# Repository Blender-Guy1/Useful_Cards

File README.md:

# Useful_Cards
This is a repository that contains cards that are useful or fun. This includes business cards that can play Pong and cards that act as simple electronics equipment for troubleshooting on the road.

## The Different Cards

### Business Card that Plays [Pong](https://en.wikipedia.org/wiki/Pong)
This went through 3 iterations before I got one that work, and 5 before I felt comfortable showing this to other people. It is a business card PCB that runs on a button cell battery and can play a any games that will run on the microcontroller. All of which is controlled with an [STM32L010F4](https://www.digikey.com/en/products/detail/stmicroelectronics/STM32L010F4P6/10063389) (which isn't exactly necessary for this application as I am running it like any other STM32 microcontroller.). More information can be found in the readme.md in the folder named "Business Card".

### Why I wanted to make Business Cards

I exhibitted at [OpenSauce 2024](https://opensauce.com/) and had the pleasure to meet [Ben Eater](https://www.youtube.com/@BenEater). He handed me a business card that was a puzzle. When a CR2025 battery was inserted, the 8 LEDs on the PCB would blink "SHAKE ME" in ASCII. Once shaken, the card wrote Ben Eater in the air. This was by far the coolest electronics idea I had ever seen. This got me thinking for a while and eventually I decided to steal his idea and make a 3D holographic business card. But that would be pretty lazy and unoriginal, so I decided on something similar that was simple. This led me to creating a business card that could play pong.

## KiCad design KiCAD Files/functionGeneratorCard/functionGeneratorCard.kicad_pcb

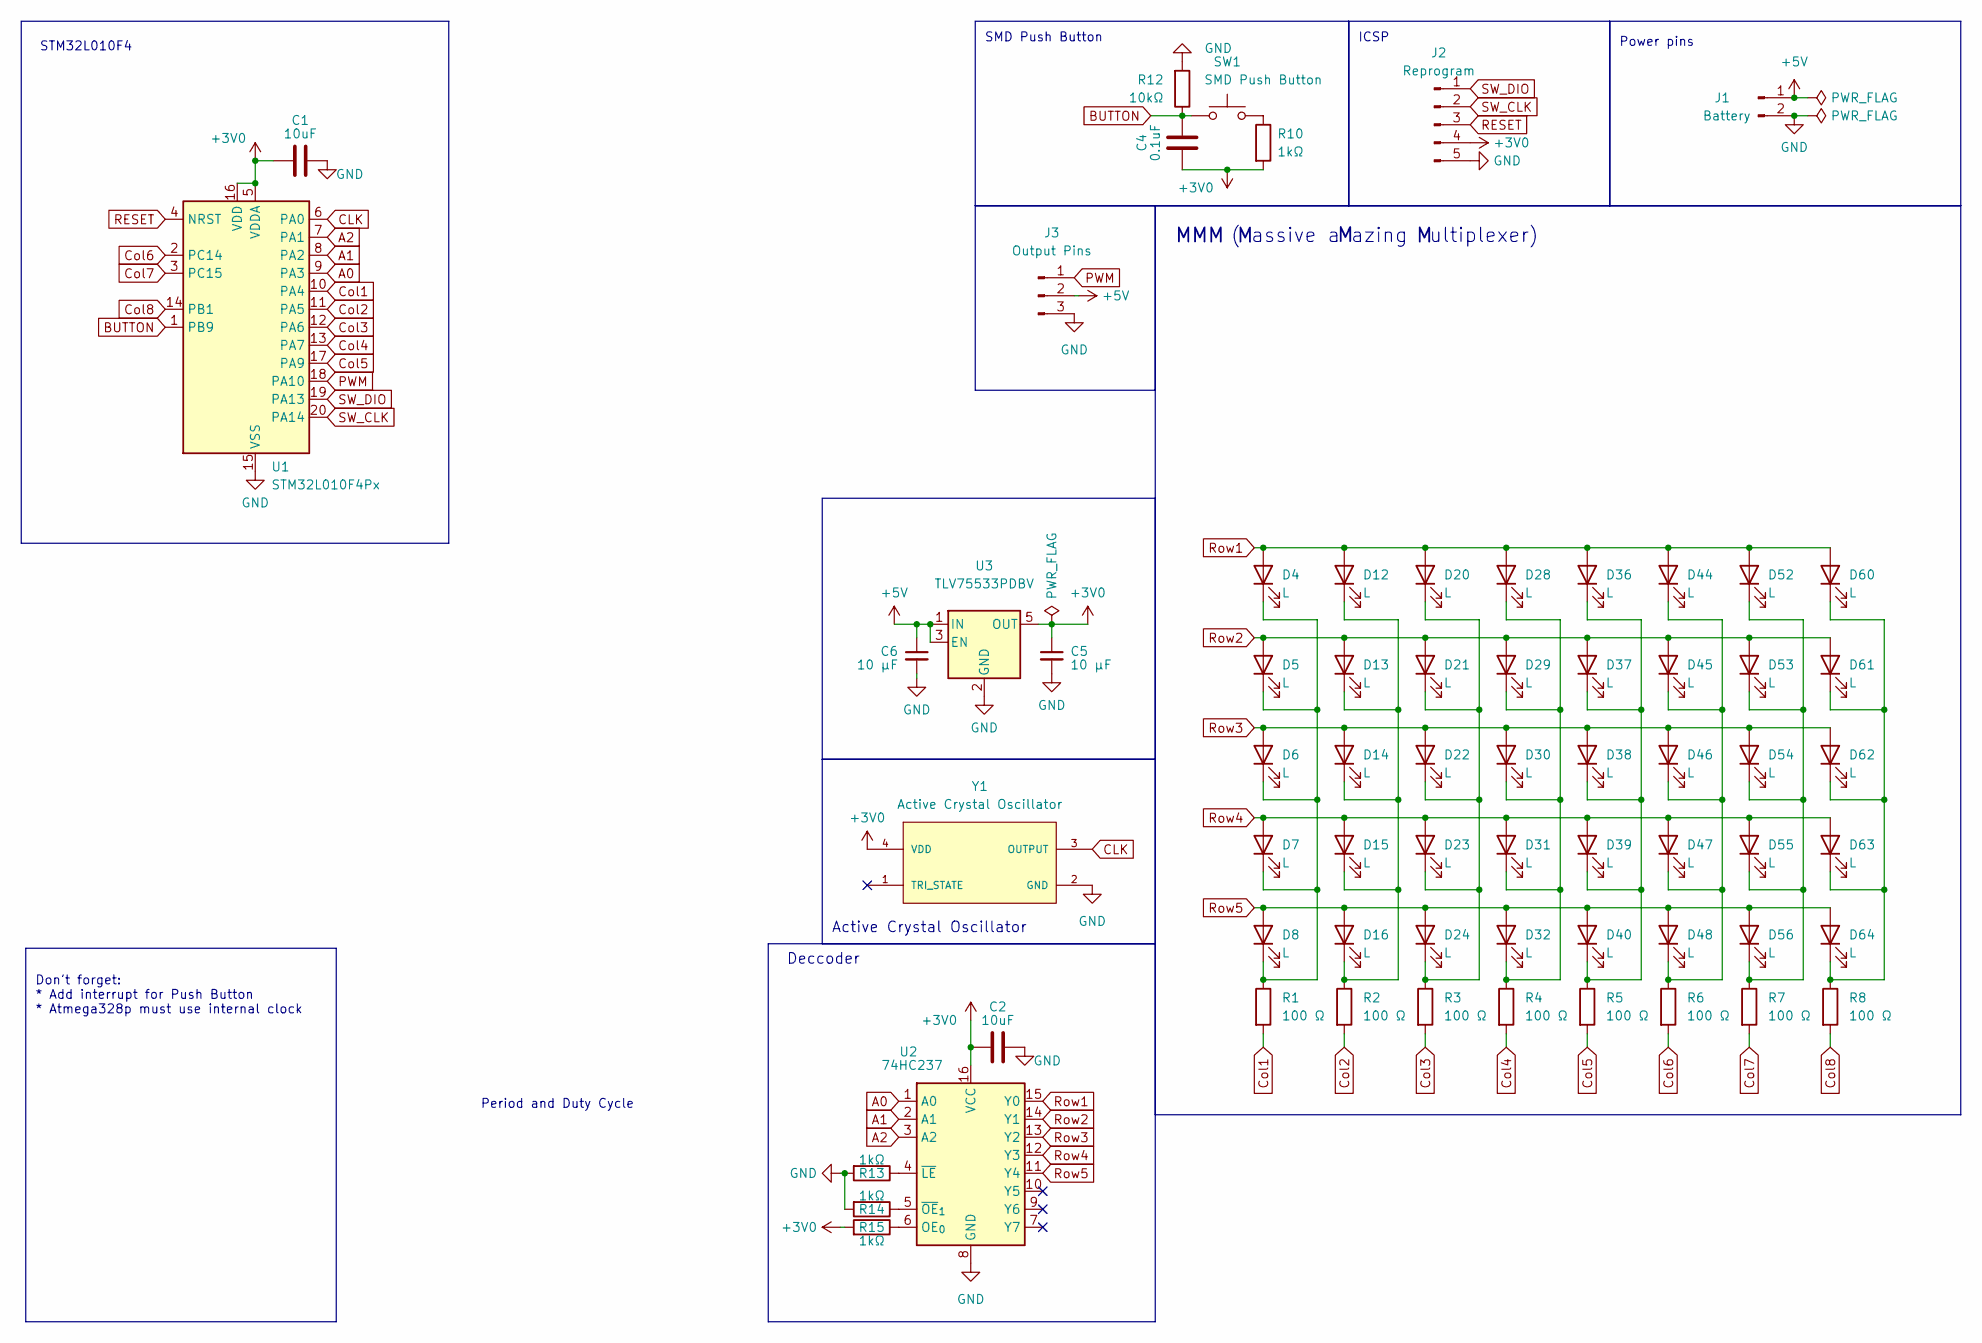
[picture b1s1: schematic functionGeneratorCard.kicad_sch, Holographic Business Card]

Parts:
C1, C2: 10uF; C_0603_1608Metric; LCSC C70225
C4: 0.1uF; C_0603_1608Metric; LCSC C1590
C5, C6: 10 µF; C_0603_1608Metric
D4, D5, D6, D7, D8, D12, D13, D14, D15, D16, D20, D21, D22, D23, D24, D28, D29, D30, D31, D32, D36, D37, D38, D39, D40, D44, D45, D46, D47, D48, D52, D53, D54, D55, D56, D60, D61, D62, D63, D64: L; LED_0805_2012Metric; LCSC C434431
J1: Battery; 2 Pin SMD (2.54)
J2: Reprogram; PinHeader_1x05_P2.54mm_Vertical
J3: Output Pins; 3 Pin SMD (2.54)
R1, R2, R3, R4, R5, R6, R7, R8: 100 Ω; R_0603_1608Metric; LCSC C3017758
R10, R13, R14, R15: 1kΩ; R_0603_1608Metric; LCSC C14676
R12: 10kΩ; R_0603_1608Metric; LCSC C15401
SW1: SMD Push Button; SW_SPST_TL3342; LCSC C2874421
U1: STM32L010F4Px; TSSOP-20_4.4x6.5mm_P0.65mm; LCSC C529415
U2: 74HC237; SOT-23-16 Thin
U3: TLV75533PDBV; SOT-23-5
Y1: Active Crystal Oscillator; active crystal oscillator; PARTREV 2017; LCSC C1857764

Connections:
+3V0: C1.1, C2.1, C4.1, C5.1, J2.4, R10.2, R15.2, U1.5 (VDDA), U1.16 (VDD), U2.16 (VCC), U3.5 (OUT), Y1.4 (VDD)
+5V: C6.1, J1.1, J3.2, U3.1 (IN), U3.3 (EN)
A0: U1.9 (PA3), U2.1 (A0)
A1: U1.8 (PA2), U2.2 (A1)
A2: U1.7 (PA1), U2.3 (A2)
BUTTON: C4.2, R12.1, SW1.1, U1.1 (PB9)
CLK: U1.6 (PA0), Y1.3 (OUTPUT)
Col1: R1.2, U1.10 (PA4)
Col2: R2.2, U1.11 (PA5)
Col3: R3.2, U1.12 (PA6)
Col4: R4.2, U1.13 (PA7)
Col5: R5.2, U1.17 (PA9)
Col6: R6.2, U1.2 (PC14)
Col7: R7.2, U1.3 (PC15)
Col8: R8.2, U1.14 (PB1)
GND: C1.2, C2.2, C5.2, C6.2, J1.2, J2.5, J3.3, R12.2, R13.2, R14.2, U1.15 (VSS), U2.8 (GND), U3.2 (GND), Y1.2 (GND)
unnamed: D4.1 (K), D5.1 (K), D6.1 (K), D7.1 (K), D8.1 (K), R1.1
unnamed: D12.1 (K), D13.1 (K), D14.1 (K), D15.1 (K), D16.1 (K), R2.1
unnamed: D20.1 (K), D21.1 (K), D22.1 (K), D23.1 (K), D24.1 (K), R3.1
unnamed: D28.1 (K), D29.1 (K), D30.1 (K), D31.1 (K), D32.1 (K), R4.1
unnamed: D36.1 (K), D37.1 (K), D38.1 (K), D39.1 (K), D40.1 (K), R5.1
unnamed: D44.1 (K), D45.1 (K), D46.1 (K), D47.1 (K), D48.1 (K), R6.1
unnamed: D52.1 (K), D53.1 (K), D54.1 (K), D55.1 (K), D56.1 (K), R7.1
unnamed: D60.1 (K), D61.1 (K), D62.1 (K), D63.1 (K), D64.1 (K), R8.1
unnamed: R10.1, SW1.2
unnamed: R15.1, U2.6 (OE_{0})
unnamed: R13.1, U2.4 (~LE)
unnamed: R14.1, U2.5 (~OE_{1})
PWM: J3.1, U1.18 (PA10)
RESET: J2.3, U1.4 (NRST)
Row1: D4.2 (A), D12.2 (A), D20.2 (A), D28.2 (A), D36.2 (A), D44.2 (A), D52.2 (A), D60.2 (A), U2.15 (Y0)
Row2: D5.2 (A), D13.2 (A), D21.2 (A), D29.2 (A), D37.2 (A), D45.2 (A), D53.2 (A), D61.2 (A), U2.14 (Y1)
Row3: D6.2 (A), D14.2 (A), D22.2 (A), D30.2 (A), D38.2 (A), D46.2 (A), D54.2 (A), D62.2 (A), U2.13 (Y2)
Row4: D7.2 (A), D15.2 (A), D23.2 (A), D31.2 (A), D39.2 (A), D47.2 (A), D55.2 (A), D63.2 (A), U2.12 (Y3)
Row5: D8.2 (A), D16.2 (A), D24.2 (A), D32.2 (A), D40.2 (A), D48.2 (A), D56.2 (A), D64.2 (A), U2.11 (Y4)
SW_CLK: J2.2, U1.20 (PA14)
SW_DIO: J2.1, U1.19 (PA13)

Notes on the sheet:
( assive a azing ultiplexer)
Don't forget: * Add interrupt for Push Button * Atmega328p must use internal clock
Deccoder
MMM
Period and Duty Cycle
Power pins
ICSP
Active Crystal Oscillator
STM32L010F4
SMD Push Button

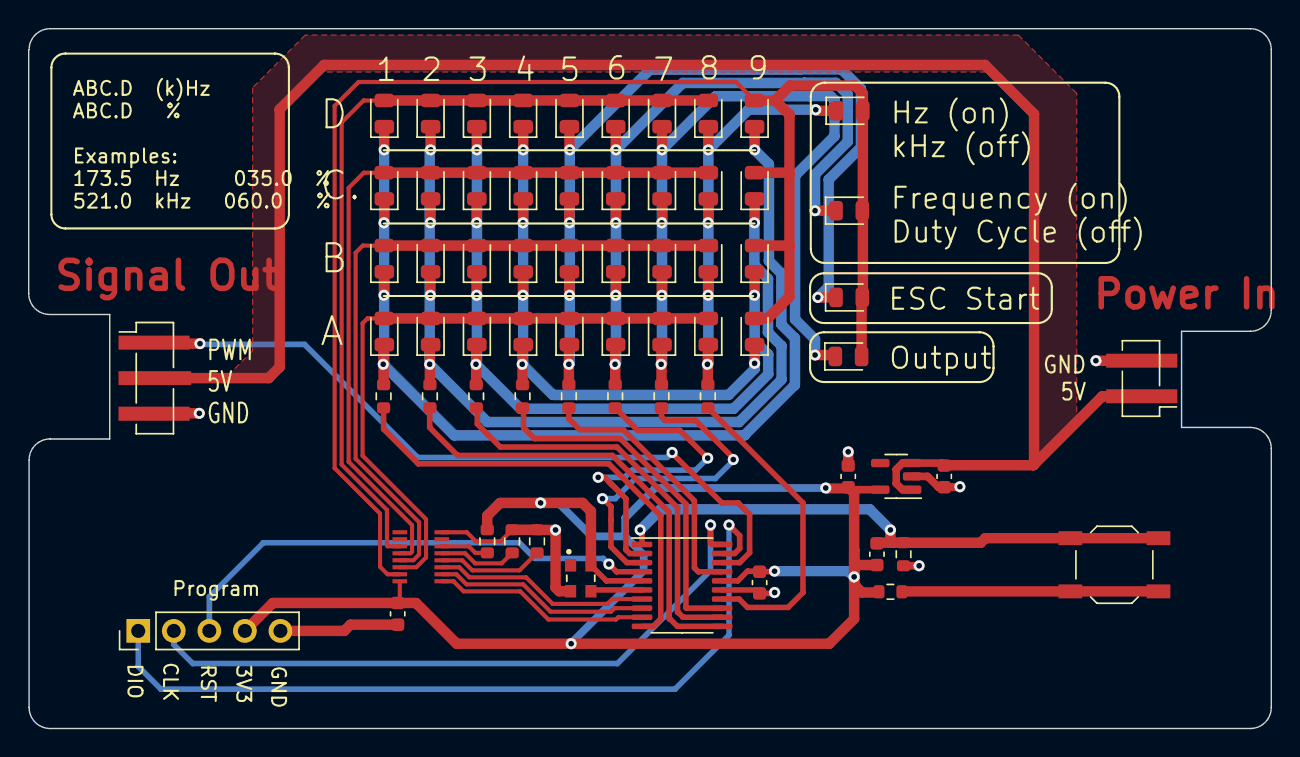
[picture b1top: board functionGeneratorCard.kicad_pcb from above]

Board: 2 copper layers, 88.8 x 50.0 mm, 66 parts (0 on the bottom side), 37 nets.

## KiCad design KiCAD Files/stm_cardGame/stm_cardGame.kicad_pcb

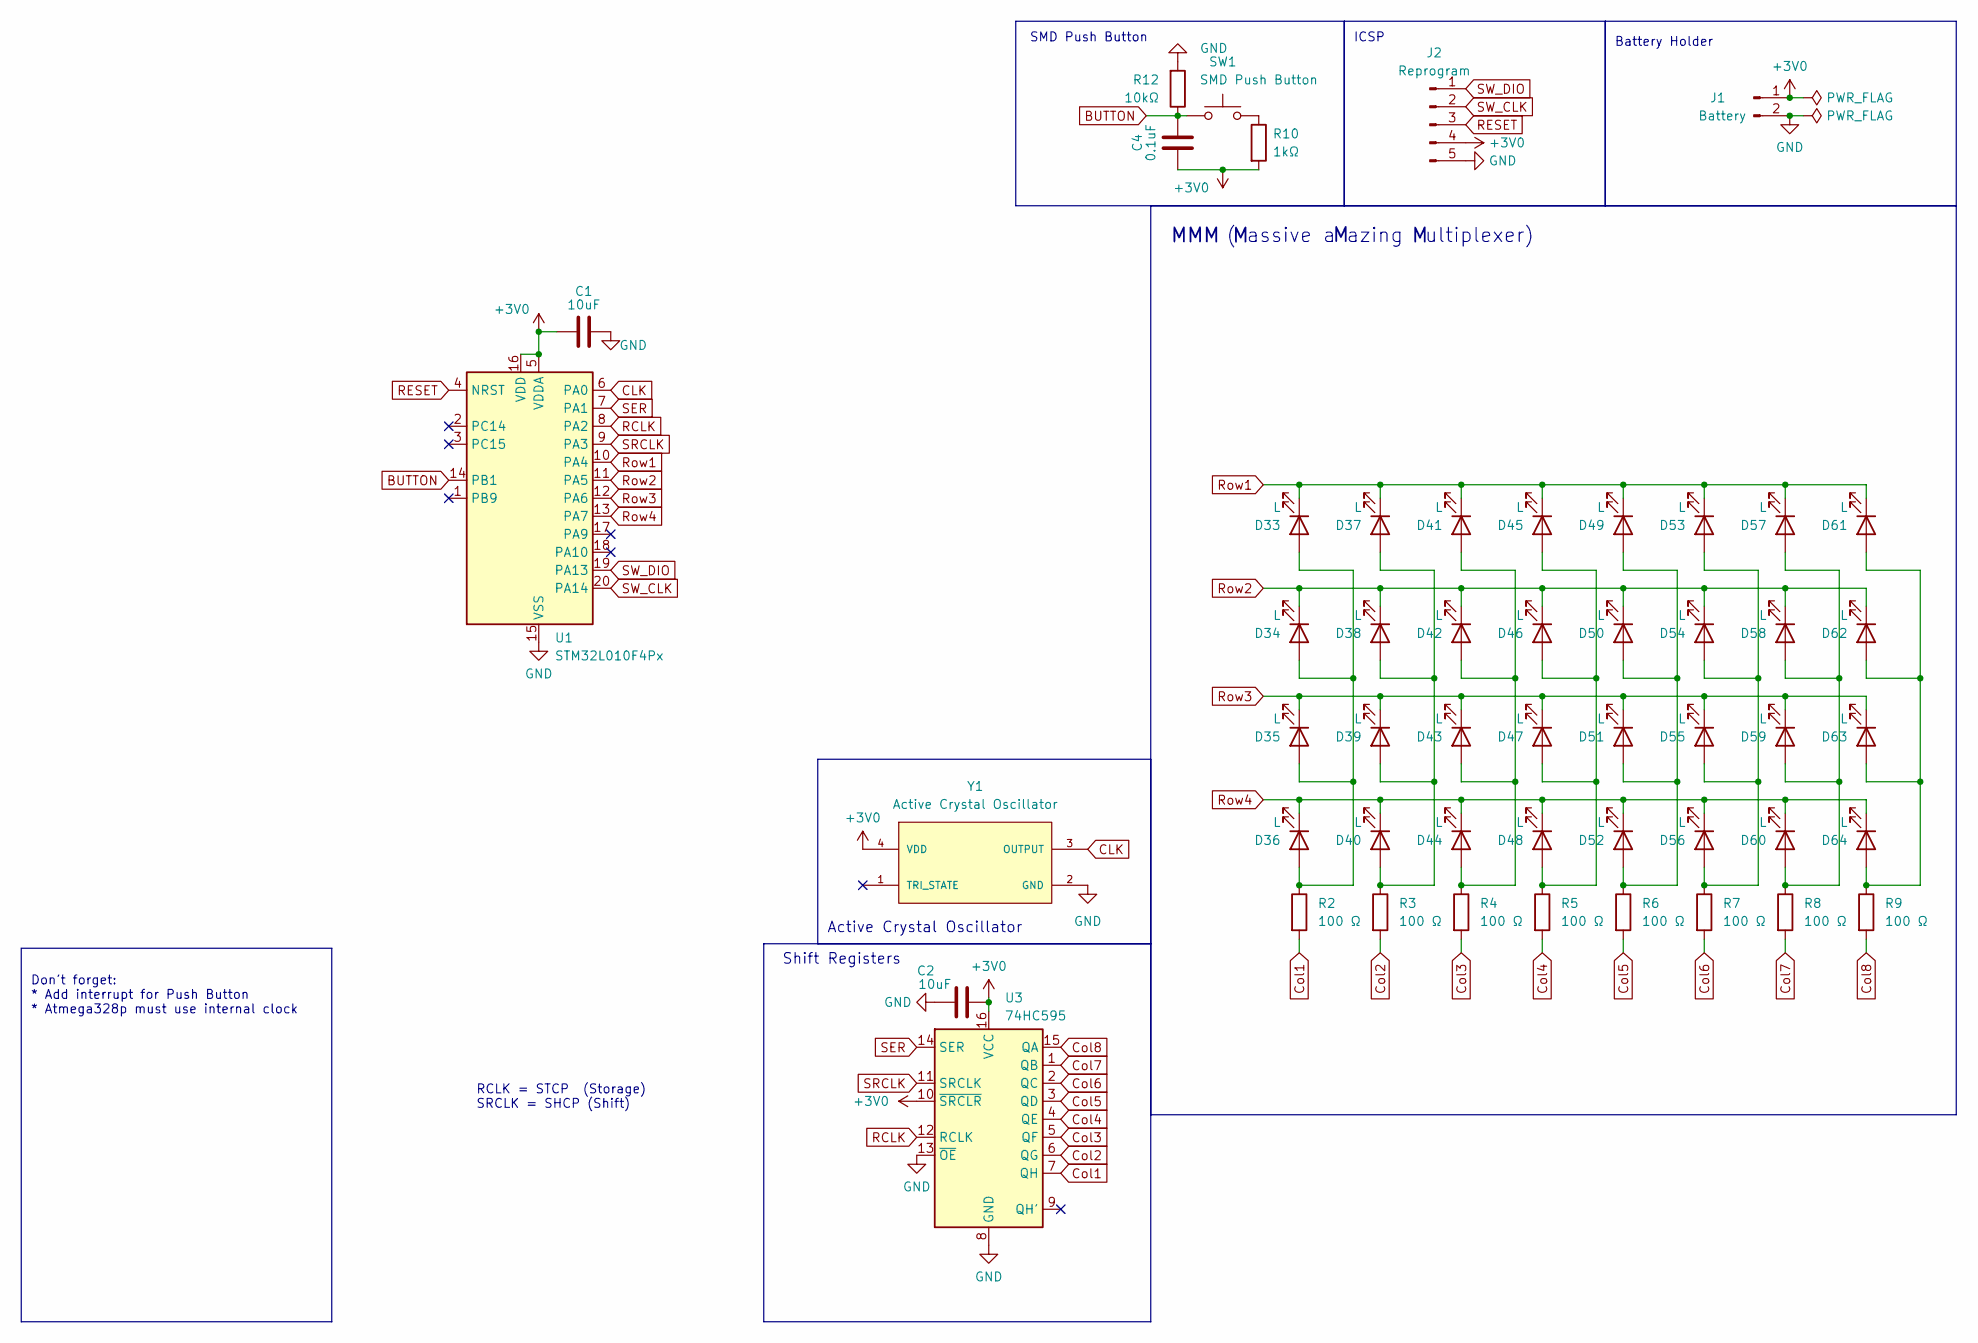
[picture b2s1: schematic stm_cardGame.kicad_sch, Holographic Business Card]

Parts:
C1, C2: 10uF; C_0603_1608Metric; LCSC C70225
C4: 0.1uF; C_0603_1608Metric; LCSC C1590
D33, D34, D35, D36, D37, D38, D39, D40, D41, D42, D43, D44, D45, D46, D47, D48, D49, D50, D51, D52, D53, D54, D55, D56, D57, D58, D59, D60, D61, D62, D63, D64: L; LED_0805_2012Metric; LCSC C434431
J1: Battery; CR2025 Circuit Board Battery Holder
J2: Reprogram; PinHeader_1x05_P2.54mm_Vertical
R2, R3, R4, R5, R6, R7, R8, R9: 100 Ω; R_0603_1608Metric; LCSC C3017758
R10: 1kΩ; R_0603_1608Metric; LCSC C14676
R12: 10kΩ; R_0603_1608Metric; LCSC C15401
SW1: SMD Push Button; SW_SPST_TL3342; LCSC C2874421
U1: STM32L010F4Px; TSSOP-20_4.4x6.5mm_P0.65mm; LCSC C529415
U3: 74HC595; TSSOP-16_4.4x5mm_P0.65mm; LCSC C273642
Y1: Active Crystal Oscillator; active crystal oscillator; PARTREV 2017; LCSC C1857764

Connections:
+3V0: C1.1, C2.2, C4.1, J1.1, J2.4, R10.2, U1.5 (VDDA), U1.16 (VDD), U3.10 (~SRCLR), U3.16 (VCC), Y1.4 (VDD)
BUTTON: C4.2, R12.1, SW1.1, U1.14 (PB1)
CLK: U1.6 (PA0), Y1.3 (OUTPUT)
Col1: R2.2, U3.7 (QH)
Col2: R3.2, U3.6 (QG)
Col3: R4.2, U3.5 (QF)
Col4: R5.2, U3.4 (QE)
Col5: R6.2, U3.3 (QD)
Col6: R7.2, U3.2 (QC)
Col7: R8.2, U3.1 (QB)
Col8: R9.2, U3.15 (QA)
GND: C1.2, C2.1, J1.2, J2.5, R12.2, U1.15 (VSS), U3.8 (GND), U3.13 (~OE), Y1.2 (GND)
unnamed: D33.2 (A), D34.2 (A), D35.2 (A), D36.2 (A), R2.1
unnamed: D37.2 (A), D38.2 (A), D39.2 (A), D40.2 (A), R3.1
unnamed: D41.2 (A), D42.2 (A), D43.2 (A), D44.2 (A), R4.1
unnamed: D45.2 (A), D46.2 (A), D47.2 (A), D48.2 (A), R5.1
unnamed: D49.2 (A), D50.2 (A), D51.2 (A), D52.2 (A), R6.1
unnamed: D53.2 (A), D54.2 (A), D55.2 (A), D56.2 (A), R7.1
unnamed: D57.2 (A), D58.2 (A), D59.2 (A), D60.2 (A), R8.1
unnamed: D61.2 (A), D62.2 (A), D63.2 (A), D64.2 (A), R9.1
unnamed: R10.1, SW1.2
RCLK: U1.8 (PA2), U3.12 (RCLK)
RESET: J2.3, U1.4 (NRST)
Row1: D33.1 (K), D37.1 (K), D41.1 (K), D45.1 (K), D49.1 (K), D53.1 (K), D57.1 (K), D61.1 (K), U1.10 (PA4)
Row2: D34.1 (K), D38.1 (K), D42.1 (K), D46.1 (K), D50.1 (K), D54.1 (K), D58.1 (K), D62.1 (K), U1.11 (PA5)
Row3: D35.1 (K), D39.1 (K), D43.1 (K), D47.1 (K), D51.1 (K), D55.1 (K), D59.1 (K), D63.1 (K), U1.12 (PA6)
Row4: D36.1 (K), D40.1 (K), D44.1 (K), D48.1 (K), D52.1 (K), D56.1 (K), D60.1 (K), D64.1 (K), U1.13 (PA7)
SER: U1.7 (PA1), U3.14 (SER)
SRCLK: U1.9 (PA3), U3.11 (SRCLK)
SW_CLK: J2.2, U1.20 (PA14)
SW_DIO: J2.1, U1.19 (PA13)

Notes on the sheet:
( assive a azing ultiplexer)
SMD Push Button
Don't forget: * Add interrupt for Push Button * Atmega328p must use internal clock
Shift Registers
MMM
RCLK = STCP (Storage) SRCLK = SHCP (Shift)
Battery Holder
ICSP
Active Crystal Oscillator

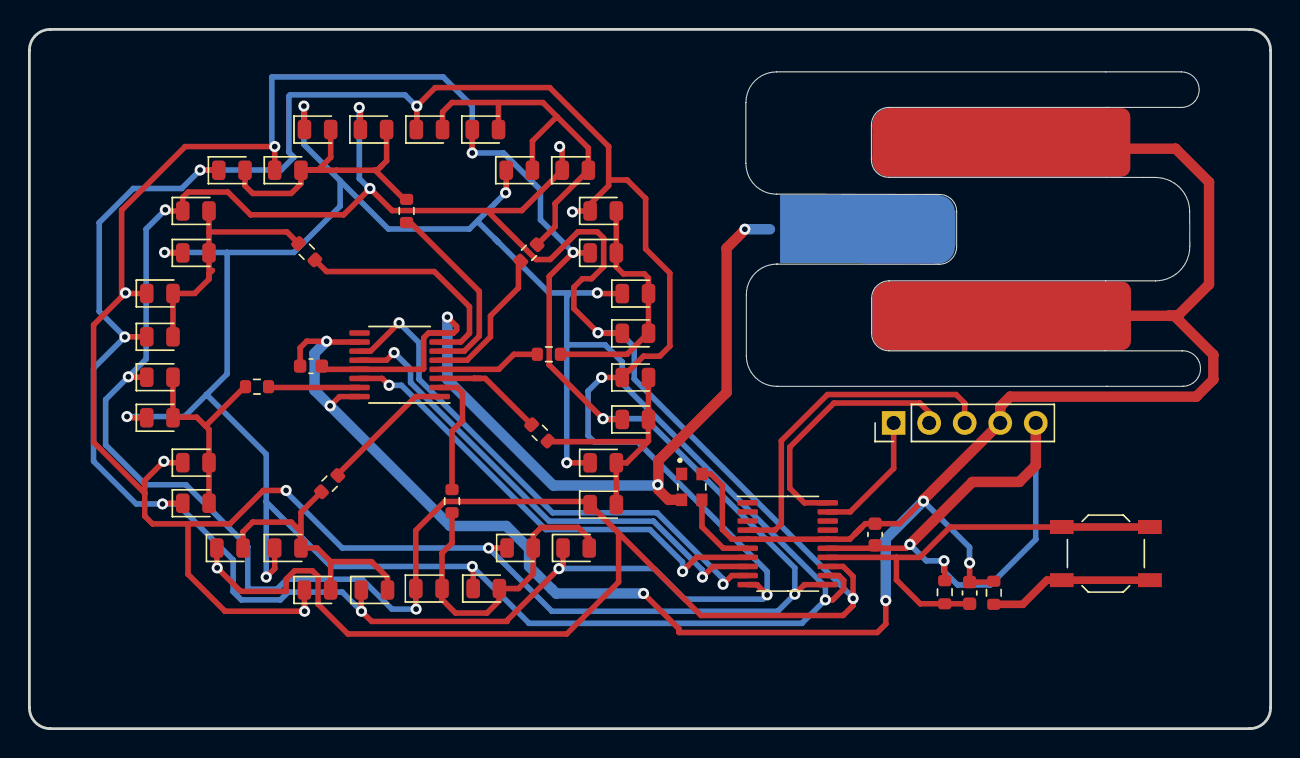
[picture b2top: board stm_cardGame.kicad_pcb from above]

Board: 2 copper layers, 88.8 x 50.0 mm, 51 parts (0 on the bottom side), 31 nets.

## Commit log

2025-03-26 Added Files
    I added the KiCAD and Gerber files for the business card, games, and function generator.
2025-03-26 Rearranged Files and Edited ReadME
    I rearranged the files so the cards are more visible and edited the ReadME.
2025-03-26 Altered ReadME
2025-03-26 Changed something for censorship
    I know my name will be in the version history, I don't care that much.
2025-03-26 Added to ReadMEs
    Added to the main readme and the business card readme.
2025-03-27 Added git ignore for useless files
2025-03-27 Edited Readmes
2025-03-28 Changes to readme
